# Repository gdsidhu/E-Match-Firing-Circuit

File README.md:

View this project on [CADLAB.io](https://cadlab.io/project/30592). 

# E-Match-Firing-Circuit
This is a repository to collaborate on the PCB design of the e-match firing circuit!

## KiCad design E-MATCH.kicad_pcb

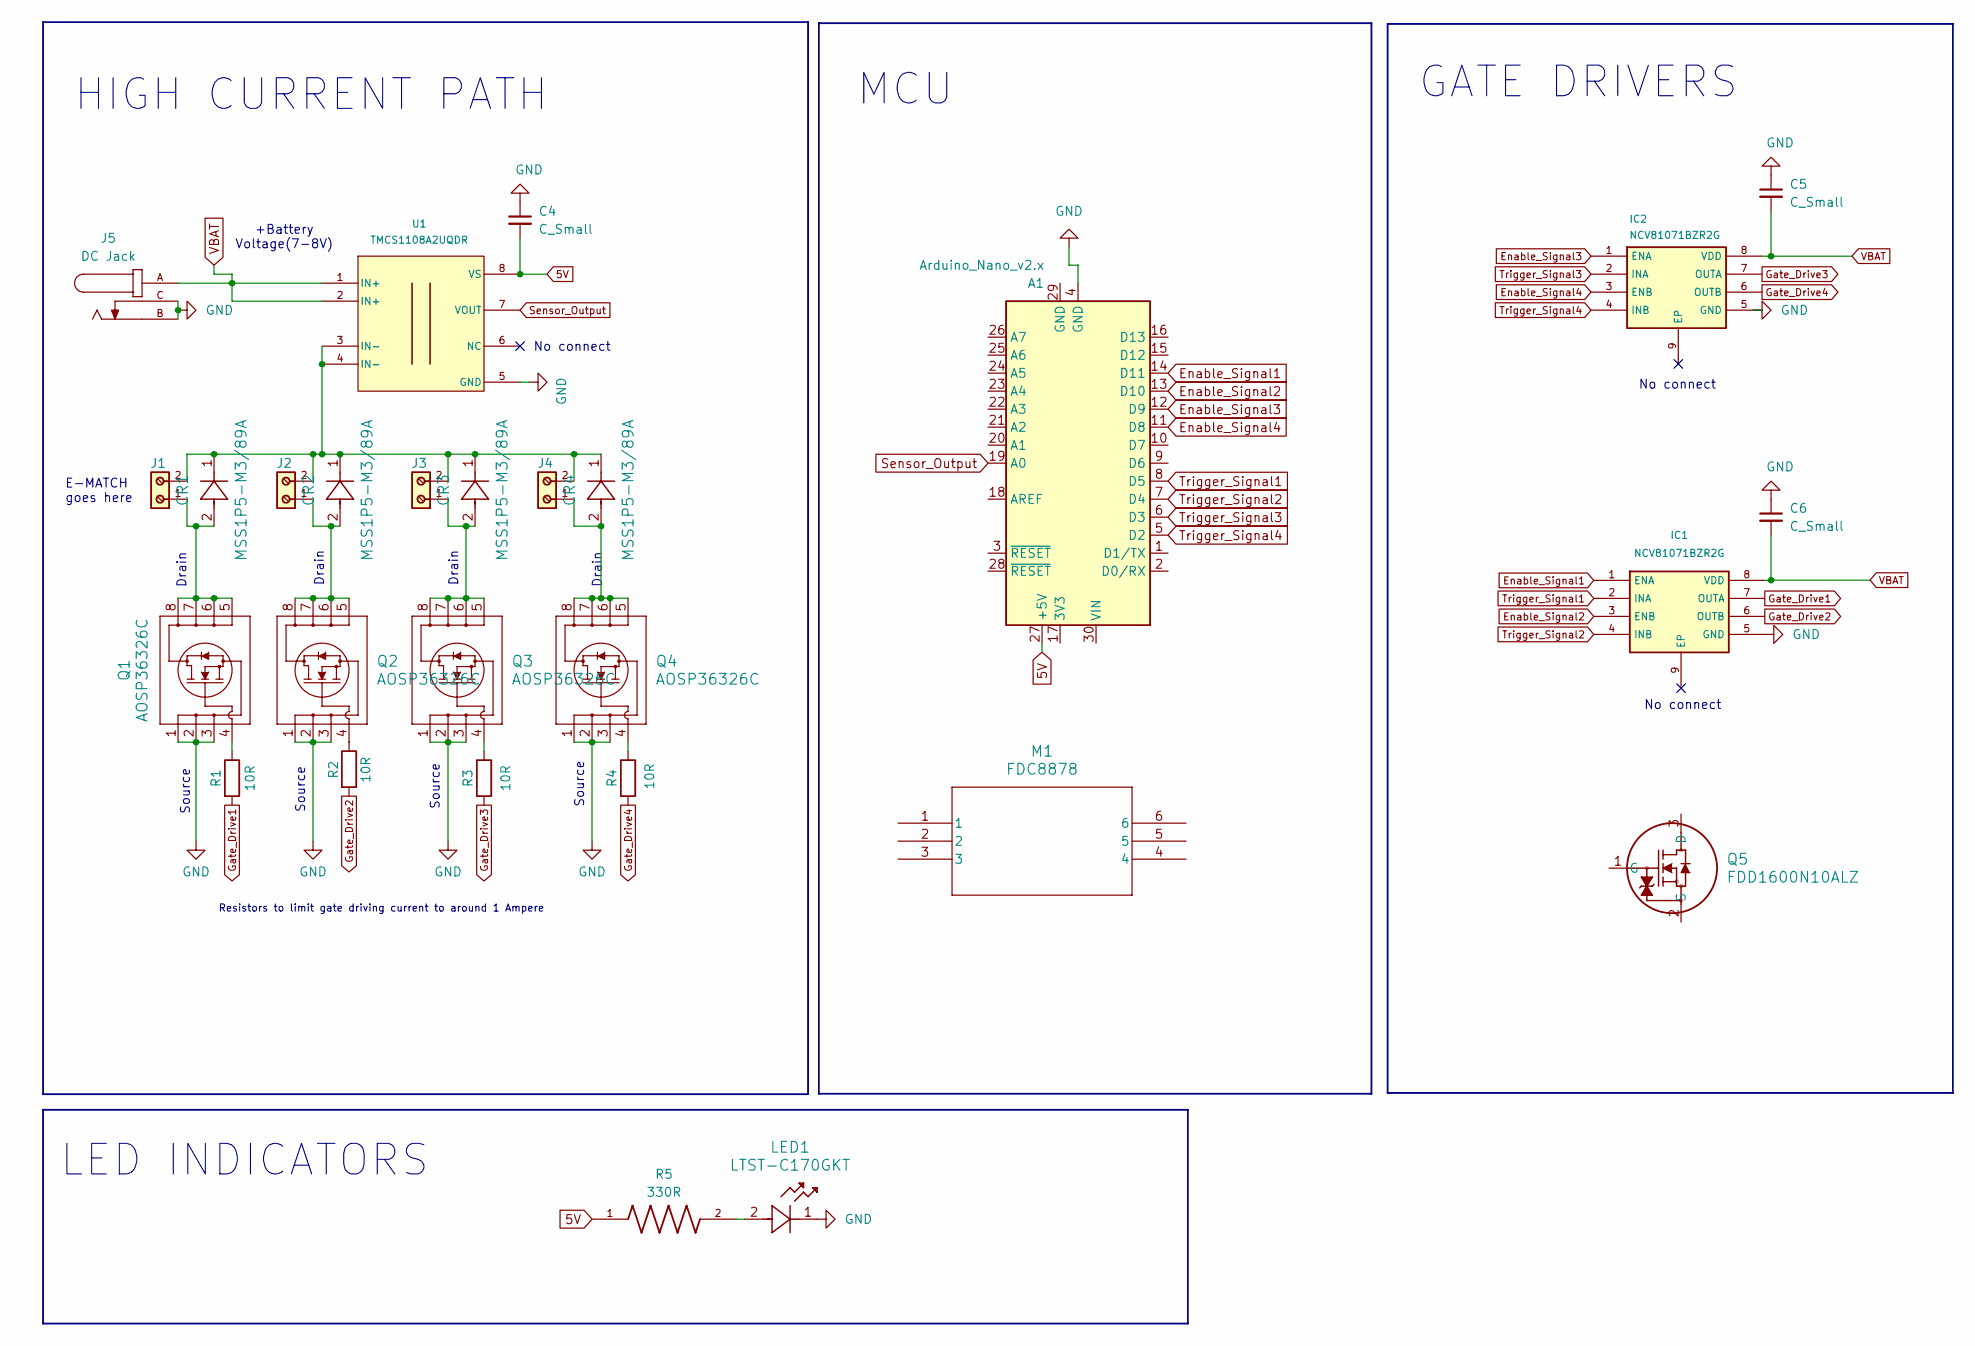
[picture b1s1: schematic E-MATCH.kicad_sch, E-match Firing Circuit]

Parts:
A1: Arduino_Nano_v2.x; Arduino_Nano
C4, C5, C6: C_Small; C_0603_1608Metric
CR1, CR2, CR3, CR4: MSS1P5-M3/89A; DIODE_MSP3V3
IC1, IC2: NCV81071BZR2G; SOP65P490X110-9N; Manufacturer_Part_Number NCV81071BZR2G
J1, J2, J3, J4: 691210910002; DigiKey_Part_Number 732-691210910002-ND
J5: DC Jack; TENSILITY_54-00130; PARTREV A; DigiKey_Part_Number 839-54-00130-ND
LED1: LTST-C170GKT; LED_LTST-C170GKT_LTO
M1: FDC8878; SuperSot6_SOT-23-6_1P6X2P9_ONS
Q1, Q2, Q3, Q4: AOSP36326C; SO8SOP-8L_AOS
Q5: FDD1600N10ALZ; TO252_FDD1600_ONS-L
R1, R2, R3, R4: 10R; RES_RC1206_YAG
R5: 330R; RESC1608X55N; DigiKey_Part_Number 311-330GRCT-ND
U1: TMCS1108A2UQDR; D0008A-IPC_A

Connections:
5V: A1.27 (+5V), C4.2, R5.1, U1.8 (VS)
Enable_Signal1: A1.14 (D11), IC1.1 (ENA)
Enable_Signal2: A1.13 (D10), IC1.3 (ENB)
Enable_Signal3: A1.12 (D9), IC2.1 (ENA)
Enable_Signal4: A1.11 (D8), IC2.3 (ENB)
GND: A1.4 (GND), C4.1, C5.1, C6.1, IC1.5 (GND), IC2.5 (GND), J5.B, J5.C, LED1.1, Q1.1, Q1.2, Q1.3, Q2.1, Q2.2, Q2.3, Q3.1, Q3.2, Q3.3, Q4.1, Q4.2, Q4.3, U1.5 (GND)
Gate_Drive1: IC1.7 (OUTA), R1.2
Gate_Drive2: IC1.6 (OUTB), R2.2
Gate_Drive3: IC2.7 (OUTA), R3.2
Gate_Drive4: IC2.6 (OUTB), R4.2
unnamed: CR1.1, CR2.1, CR3.1, CR4.1, J1.2, J2.2, J3.2, J4.2, U1.3 (IN-), U1.4 (IN-)
unnamed: CR1.2, J1.1, Q1.5, Q1.6, Q1.7, Q1.8
unnamed: CR2.2, J2.1, Q2.5, Q2.6, Q2.7, Q2.8
unnamed: CR3.2, J3.1, Q3.5, Q3.6, Q3.7, Q3.8
unnamed: CR4.2, J4.1, Q4.5, Q4.6, Q4.7, Q4.8
unnamed: LED1.2, R5.2
unnamed: Q1.4, R1.1
unnamed: Q2.4, R2.1
unnamed: Q3.4, R3.1
unnamed: Q4.4, R4.1
Sensor_Output: A1.19 (A0), U1.7 (VOUT)
Trigger_Signal1: A1.8 (D5), IC1.2 (INA)
Trigger_Signal2: A1.7 (D4), IC1.4 (INB)
Trigger_Signal3: A1.6 (D3), IC2.2 (INA)
Trigger_Signal4: A1.5 (D2), IC2.4 (INB)
VBAT: C5.2, C6.2, IC1.8 (VDD), IC2.8 (VDD), J5.A, U1.1 (IN+), U1.2 (IN+)

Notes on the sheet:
Source
MCU
Drain
No connect
Resistors to limit gate driving current to around 1 Ampere
E-MATCH goes here
GATE DRIVERS
LED INDICATORS
+Battery Voltage(7-8V)
HIGH CURRENT PATH

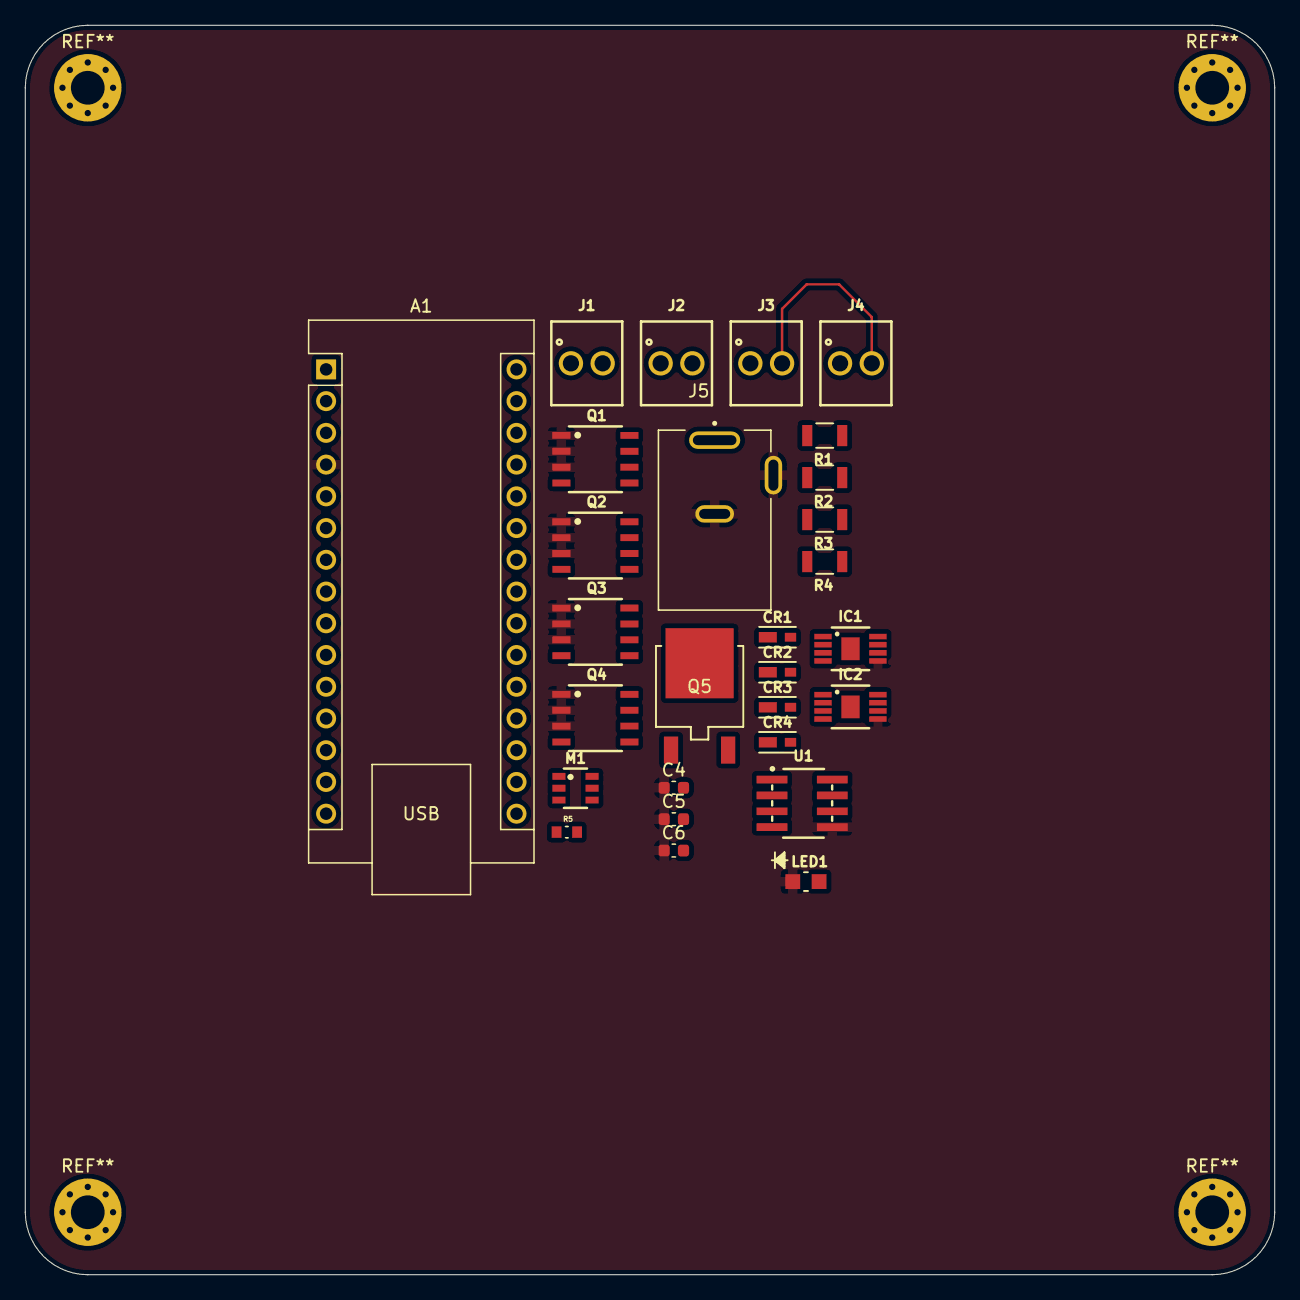
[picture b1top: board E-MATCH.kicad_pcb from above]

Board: 4 copper layers, 100.0 x 100.0 mm, 28 parts (0 on the bottom side), 26 nets.

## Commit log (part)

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2025-11-23 All PCB Design Files
2025-11-23 Added the default KICAD backup files to .gitignore
    The KICAD backup files are just partial backup files but we won't be needing them anymore because full version control would be taken care of by Github itself.
2025-11-23 updated .gitignore
2025-11-25 Updating Schematic Test
2025-11-25 gitignoring .lck files
2025-11-25 Resistor and Screw Terminal E-Cad Models were added!
    Additionally, some progress was made in the schematic.
2025-11-29 Added Text-Descriptions
2025-11-29 Neat placement for schematic
2025-11-29 New Diode- smaller footprint
2025-12-02 Added folder for software
2025-12-04 New Mosfet plus linked some 3-d models
2025-12-04 More 3-d models
2025-12-05 linked 3-d models
2025-12-07 A lot of changes :)
2025-12-22 routing
2025-12-24 Do not use colons in file name.
2026-01-25 Led-indicator file structure
2026-01-26 2 layers to 4 layers
2026-01-27 Added SMD-LED footprint
2026-01-27 Associated Led with correct 3d model
2026-01-27 edited current sensor symbol
2026-01-28 Schematic Cleanup
2026-01-29 SMD_Resistor added
2026-01-29 3d model reassociation
2026-01-29 added the Led and resistor to 5V
2026-01-31 Schematic pdf now in the repository
2026-02-07 modified some footprints
2026-02-11 Cleaned a few footprints
2026-02-11 added a decoupling capacitor
2026-02-12 made minor adjustments in both schematic and pcb layout
2026-02-22 some changes
